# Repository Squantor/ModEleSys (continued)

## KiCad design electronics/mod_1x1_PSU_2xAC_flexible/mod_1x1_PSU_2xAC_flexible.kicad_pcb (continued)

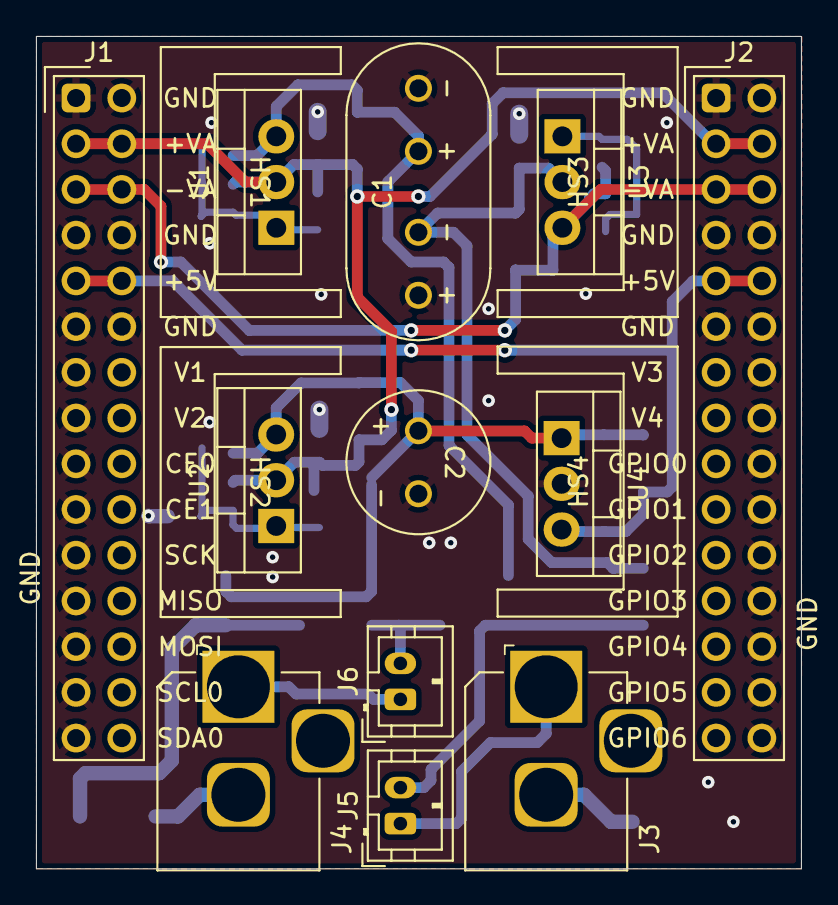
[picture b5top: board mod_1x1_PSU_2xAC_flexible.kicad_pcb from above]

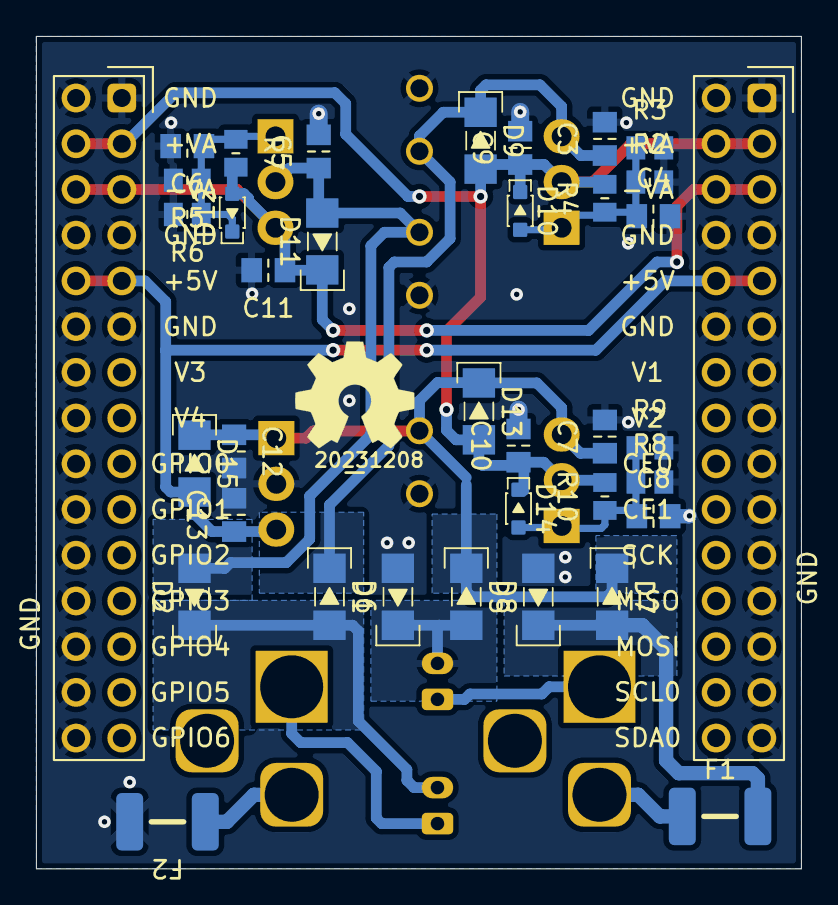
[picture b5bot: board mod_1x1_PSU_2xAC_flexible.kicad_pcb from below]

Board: 2 copper layers, 42.5 x 46.2 mm, 53 parts (37 on the bottom side), 17 nets.

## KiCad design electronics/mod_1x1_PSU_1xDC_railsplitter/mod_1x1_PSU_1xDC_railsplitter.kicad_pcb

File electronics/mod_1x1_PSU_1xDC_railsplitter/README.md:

# ModEleSys PSU
ModEleSys 1x1 module Powersupply. One DC input that is fed into a LD1117 LDO, then railsplit with a LM317/LM337 railsplitter, this creates a virtual earth, another LD1117 is present to create a 5V supply, and it uses this virtual ground.
## TODO's
Still some things need to be done:
* Schematic entry
* Place and route
* Review
* Production
* Assemble
* Test & characterise
* update Readme.md with pictures and BOM
## BOM
This is a list of hardware components. If just mentioned a generic component like a 1K 0402 resistor, just name it as such, free to substitute. If you need some special integrated IC's show some sources like Mouser, Digikey, Farnell, or LCSC
* D2PAK (TO-252) LD1117, LM317 and LM337
* SMA cased diodes
* Mostly ceramic capacitors used
* 500mA trip polyfuses in 1812 SMT housing

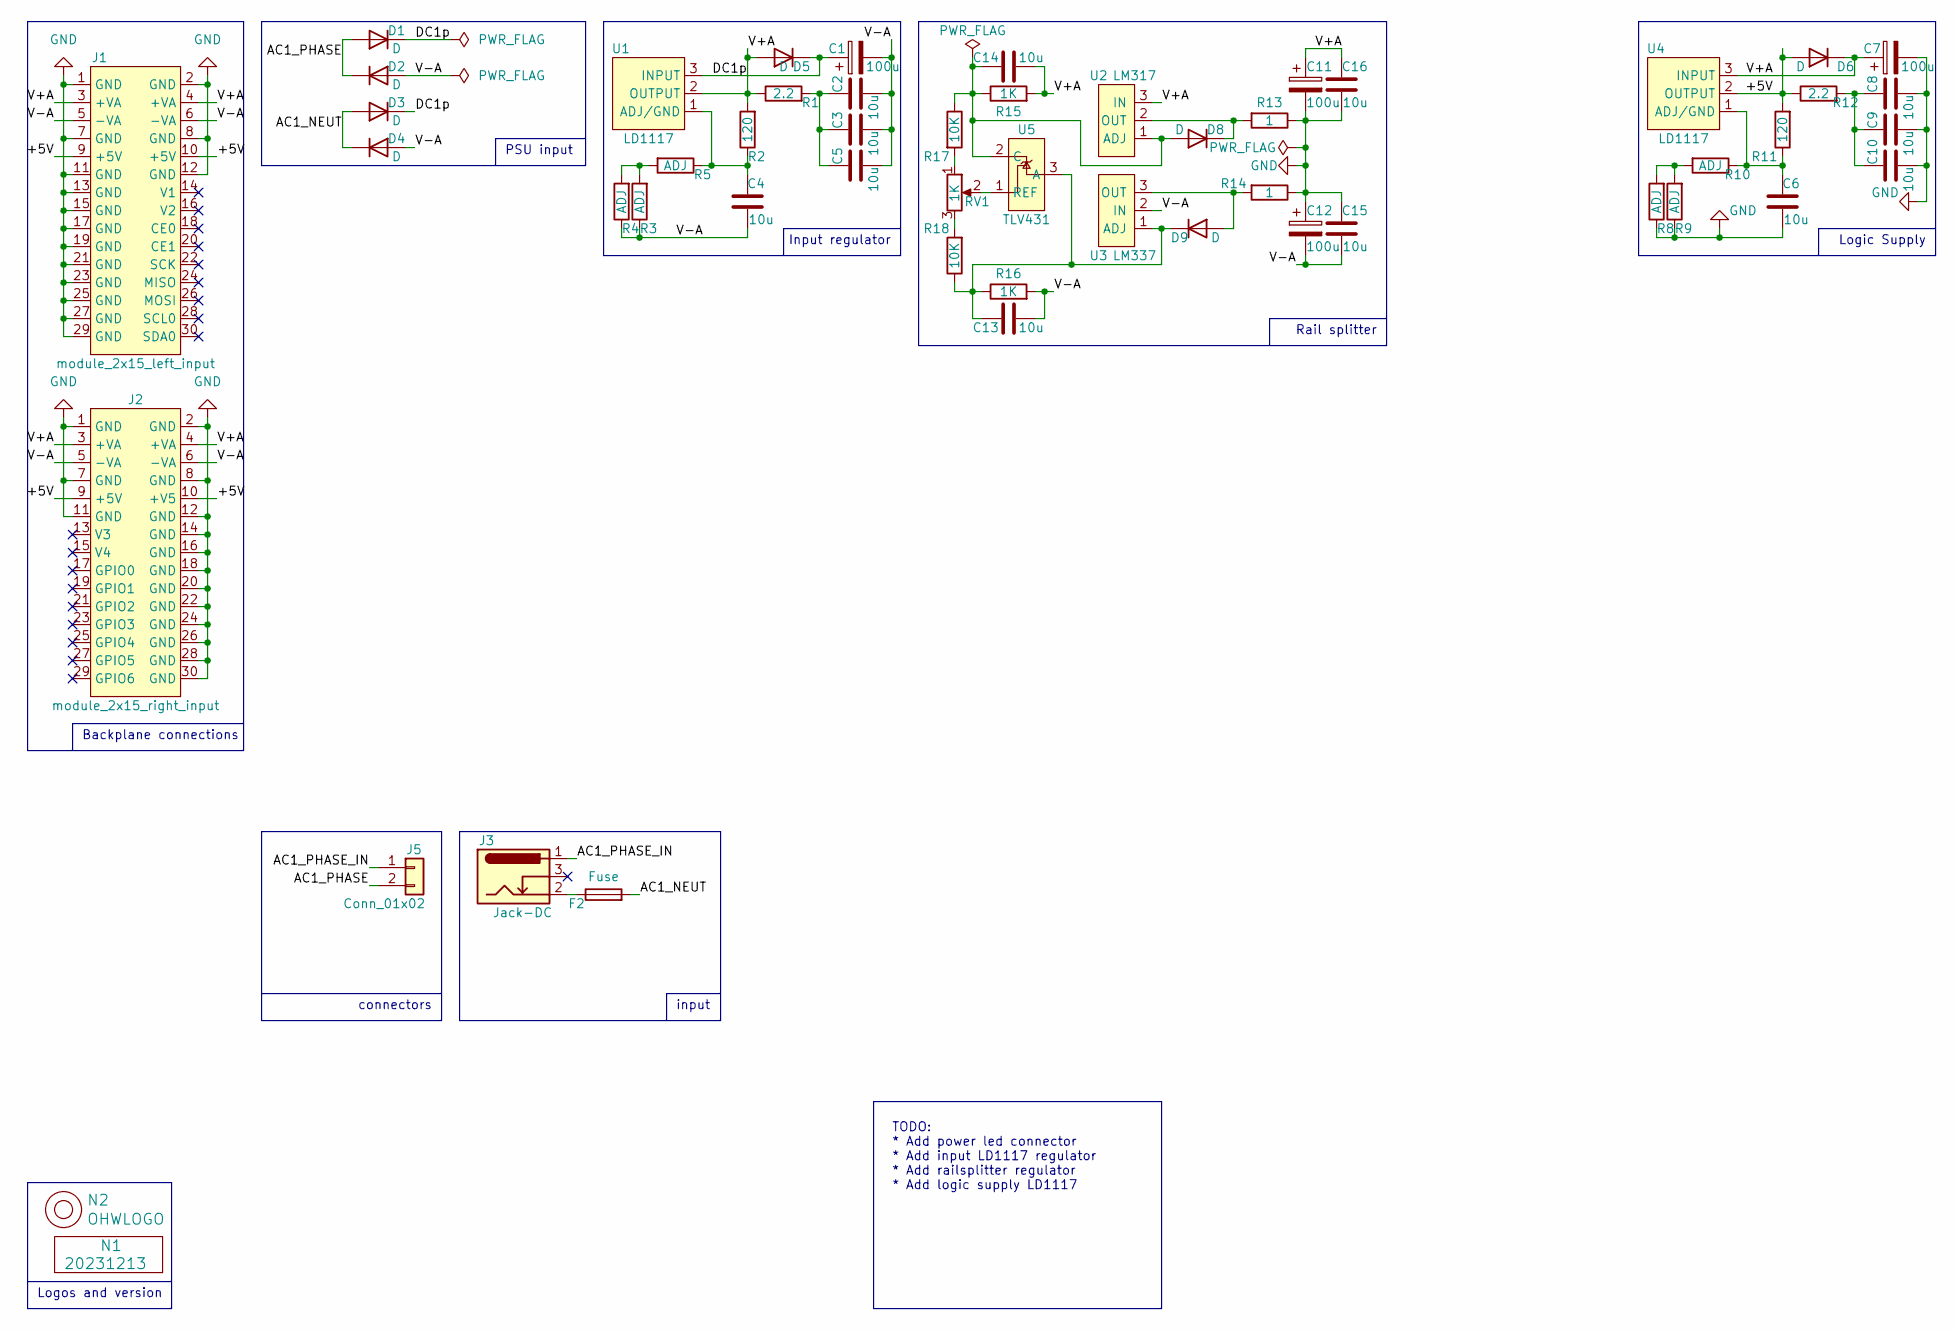
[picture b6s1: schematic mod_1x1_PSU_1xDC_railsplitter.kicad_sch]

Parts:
C1, C11, C12: 100u; C-050-100-elco-lying_flip
C2, C3, C4, C5, C6, C8, C9, C10: 10u; C_0805
C7: 100u; C-050-100-elco-lying
C13, C14, C15, C16: 10u; C_0603
D1, D2, D3, D4: D; SOD-123F-hand
D5, D6, D8, D9: D; SOD-323-onsemi
F2: Fuse; F_1812-bourns
J1: module_2x15_left_input; module_2x15_left
J2: module_2x15_right_input; module_2x15_right
J3: Jack-DC; BarrelJack_Horizontal_Holed
J5: Conn_01x02; JST_PH_B2B-PH-K_1x02_P2.00mm_Vertical
N1: 20231213; Label_Generic
N2: OHWLOGO; OSHW-Symbol_6.7x6mm_SilkScreen
R1, R12: 2.2; R_0805+0603
R2, R11: 120; R_0805+0603
R3, R4, R5, R8, R9, R10: ADJ; R_0805+0603
R13, R14: 1; R_0805+0603
R15, R16: 1K; R_0603_hand
R17, R18: 10K; R_0603_hand
RV1: 1K; POT-23A-BI_technologies
U1, U4: LD1117; TO-252_D-PAK_IRF
U2: LM317; TO-252_D-PAK_IRF
U3: LM337; TO-252_D-PAK_IRF
U5: TLV431; SOT23-3

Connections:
/+5V: D6.2 (A), J1.9 (+5V), J1.10 (+5V), J2.9 (+5V), J2.10 (+V5), R11.2, R12.1, U4.2 (OUTPUT)
/AC1_NEUT: D3.2 (A), D4.1 (K), F2.2
/AC1_PHASE: D1.2 (A), D2.1 (K), J5.2
/AC1_PHASE_IN: J3.1, J5.1
/DC1p: C1.1, D1.1 (K), D3.1 (K), D5.1 (K), U1.3 (INPUT)
/V+A: C7.1, C11.1, C14.2, C16.2, D5.2 (A), D6.1 (K), J1.3 (+VA), J1.4 (+VA), J2.3 (+VA), J2.4 (+VA), R1.1, R2.2, R15.2, U1.2 (OUTPUT), U2.3 (IN), U4.3 (INPUT)
/V-A: C1.2, C2.2, C3.2, C4.1, C5.2, C12.2, C13.2, C15.1, D2.2 (A), D4.2 (A), J1.5 (-VA), J1.6 (-VA), J2.5 (-VA), J2.6 (-VA), R3.1, R4.1, R16.2, U3.2 (IN)
GND: C6.1, C7.2, C8.2, C9.2, C10.2, C11.2, C12.1, C15.2, C16.1, J1.1 (GND), J1.2 (GND), J1.7 (GND), J1.8 (GND), J1.11 (GND), J1.12 (GND), J1.13 (GND), J1.15 (GND), J1.17 (GND), J1.19 (GND), J1.21 (GND), J1.23 (GND), J1.25 (GND), J1.27 (GND), J1.29 (GND), J2.1 (GND), J2.2 (GND), J2.7 (GND), J2.8 (GND), J2.11 (GND), J2.12 (GND), J2.14 (GND), J2.16 (GND), J2.18 (GND), J2.20 (GND), J2.22 (GND), J2.24 (GND), J2.26 (GND), J2.28 (GND), J2.30 (GND), R8.1, R9.1, R13.1, R14.1
unnamed: C2.1, C3.1, C5.1, R1.2
unnamed: C8.1, C9.1, C10.1, R12.2
unnamed: C14.1, D8.2 (A), R15.1, R17.1, U2.1 (ADJ), U5.2 (C)
unnamed: D8.1 (K), R13.2, U2.2 (OUT)
unnamed: D9.2 (A), R14.2, U3.3 (OUT)
unnamed: C13.1, D9.1 (K), R16.1, R18.1, U3.1 (ADJ), U5.3 (A)
unnamed: F2.1, J3.2
unnamed: R3.2, R4.2, R5.2
unnamed: R8.2, R9.2, R10.2
unnamed: R17.2, RV1.1
unnamed: R18.2, RV1.3
unnamed: C4.2, R2.1, R5.1, U1.1 (ADJ/GND)
unnamed: C6.2, R10.1, R11.1, U4.1 (ADJ/GND)
unnamed: RV1.2, U5.1 (REF)

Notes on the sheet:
Backplane connections
input
Logic Supply
Logos and version
PSU input
connectors
Input regulator
TODO: * Add power led connector * Add input LD1117 regulator * Add railsplitter regulator * Add logic supply LD1117
Rail splitter

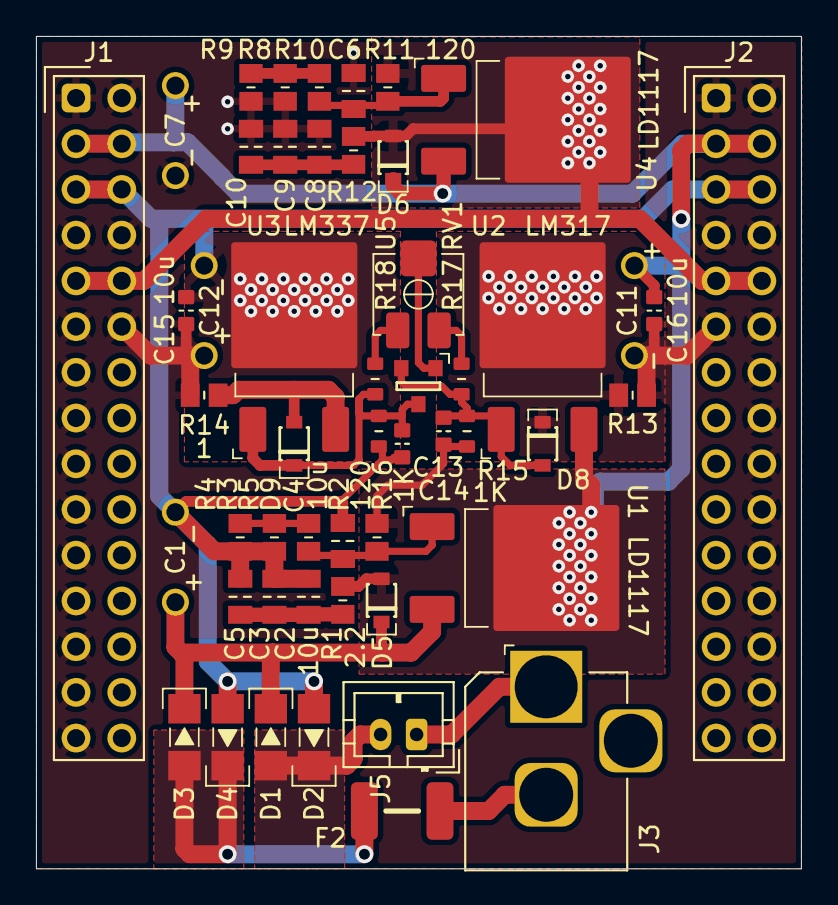
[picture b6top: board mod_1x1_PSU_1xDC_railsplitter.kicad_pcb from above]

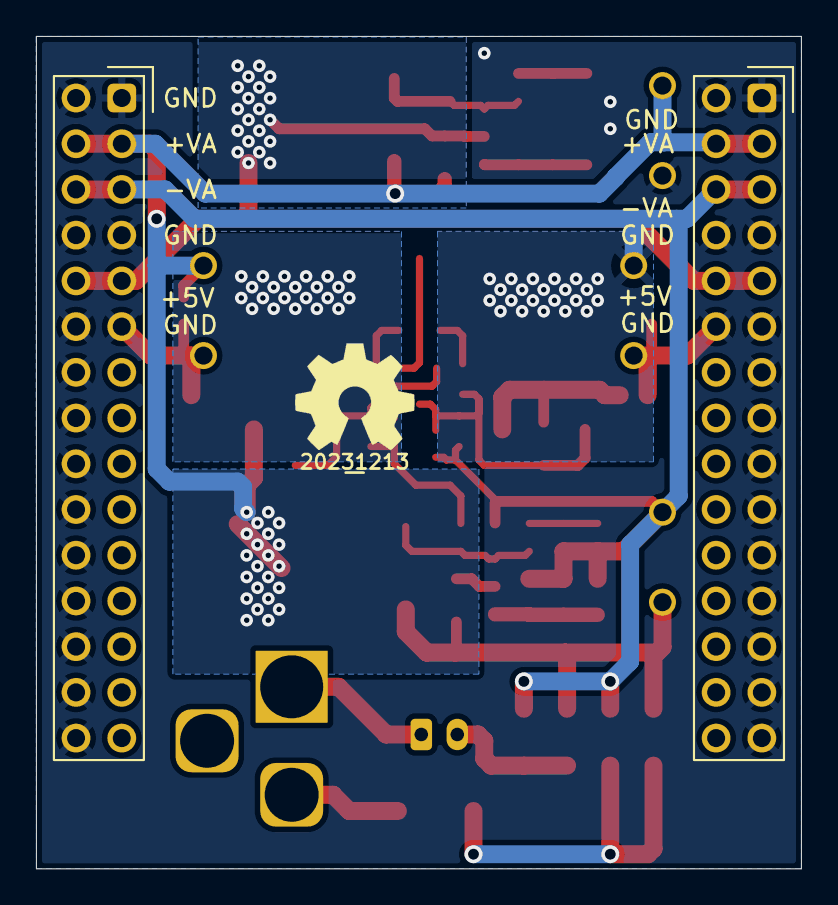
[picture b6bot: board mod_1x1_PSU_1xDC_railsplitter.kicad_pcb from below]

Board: 2 copper layers, 42.5 x 46.2 mm, 53 parts (2 on the bottom side), 22 nets.

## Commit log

2023-09-16 initial population of documentation files
2023-09-16 fixed broken link
2023-09-16 moving electronics and mechanical bits
2023-09-16 added 1x1 PSU 1xDC with railsplitter start project
2023-09-20 updated PCB library with new parts
2023-09-20 added lock files
2023-09-20 WIP initial LDO schematic, updated PCB library
2023-09-24 WIP schematic entry
2023-09-27 small schematic updates and place and route
2023-09-28 WIP placement, done schematic
2023-09-29 further placing and routing
2023-10-02 routing completed
2023-10-03 completed silk placement, few values adjusted
2023-10-25 updated PCB with newer/different footprints
2023-11-23 small changes for producability and form and fit
2023-12-03 updated components and fixed warnings
2023-12-06 updated library
2023-12-06 fixing DRC errors
2023-12-08 imported aisler budget design rules, fixed all DRC errors resulting from that
2023-12-08 fixed last DRC errors
2023-12-13 final changes and some extra vias
2024-01-08 WIP updated to new component libraries
2024-03-25 started with ModEleSysV2 AC symmetrical PSU
2024-03-28 WIP placement of parts and reducing sizes, it is a bit cramped
2024-03-29 done, needs review in between
2024-04-20 added Battery powered mini powersupply
2024-04-21 silk placement done, ready for review
2024-04-21 created Assymetrical AC input PSU for some other applications
2024-04-21 added second regulator
2024-04-22 silk placement done
2024-04-24 reviewed and different placement of switch and power input
2024-04-24 reviewed
2024-04-26 updated versionnumbers
2024-04-26 fixed small issue with connectors
2024-04-26 updated gitignore for newer freecad versions
2024-04-26 updated alubox drill guide, added drillguide for ModEleSysV2
2025-03-14 updated PCB with easier to place components and added more output capacitance
2025-03-14 some more PCB modifications, changing output caps to larger values
2025-04-01 preparations for production
2026-01-06 added backplane, updated kicad file versions
2026-01-06 updated backplane with 2x3 XH connectors
2026-01-07 changed power on/off connector on backplane
2026-01-07 rename of project
2026-01-16 reviewed and updated PCB's
2026-01-18 Updated for production
